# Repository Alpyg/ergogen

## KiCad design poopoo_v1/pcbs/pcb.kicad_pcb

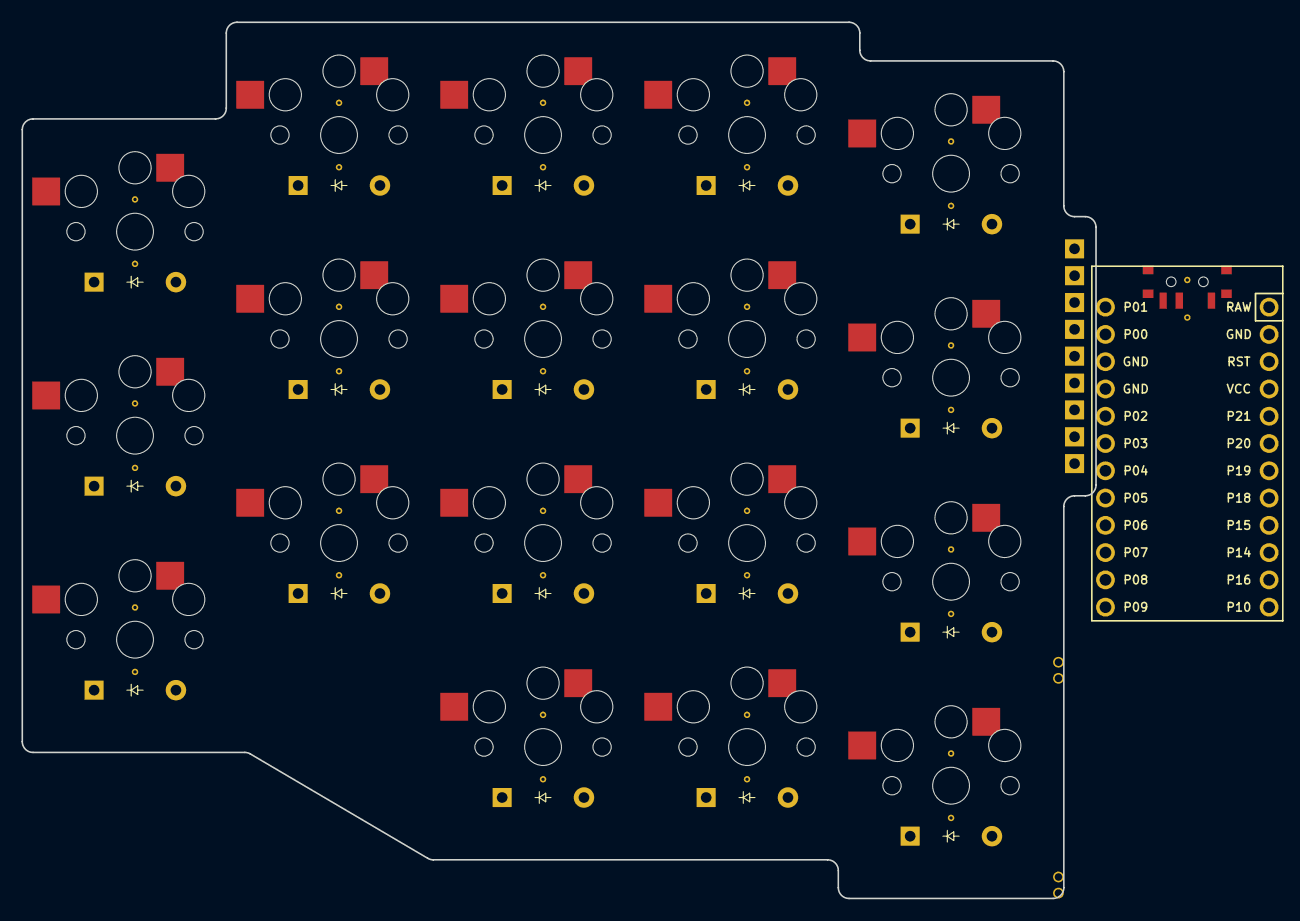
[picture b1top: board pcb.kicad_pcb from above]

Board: 2 copper layers, 100.0 x 81.6 mm, 37 parts (0 on the bottom side), 28 nets, no tracks yet.

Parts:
D1, D2, D3, D4, D5, D6, D7, D8, D9, D10, D11, D12, D13, D14, D15, D16, D17, D18: ComboDiode
MCU1: ProMicro
S1, S2, S3, S4, S5, S6, S7, S8, S9, S10, S11, S12, S13, S14, S15, S16, S17, S18: PG1350

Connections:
GND: MCU1.2, MCU1.15, MCU1.16
col_far: S15.2, S16.2, S17.2, S18.2
col_index: S11.2, S12.2, S13.2, S14.2
col_middle: S7.2, S8.2, S9.2, S10.2
col_pinky: S1.2, S2.2, S3.2
col_ring: S4.2, S5.2, S6.2
home_col_far: D17.2, S17.1
home_col_index: D13.2, S13.1
home_col_middle: D9.2, S9.1
home_col_pinky: D2.2, S2.1
home_col_ring: D5.2, S5.1
inner_col_far: D16.2, S16.1
inner_col_index: D12.2, S12.1
inner_col_middle: D8.2, S8.1
inner_col_pinky: D1.2, S1.1
inner_col_ring: D4.2, S4.1
outer_col_far: D18.2, S18.1
outer_col_index: D14.2, S14.1
outer_col_middle: D10.2, S10.1
outer_col_pinky: D3.2, S3.1
outer_col_ring: D6.2, S6.1
row_home: D2.1, D5.1, D9.1, D13.1, D17.1
row_inner: D1.1, D4.1, D8.1, D12.1, D16.1
row_outer: D3.1, D6.1, D10.1, D14.1, D18.1
row_thumb: D7.1, D11.1, D15.1
thumb_col_far: D15.2, S15.1
thumb_col_index: D11.2, S11.1
thumb_col_middle: D7.2, S7.1

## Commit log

2023-01-16 Added Ben Vallack's footprints
2023-01-28 Revert "Added Ben Vallack's footprints"
    This reverts commit 423b156d2d0c8febfb8dc57614209ea511b82ca3.
2023-10-22 poopoo
2024-06-14 PooVoyager v1
2024-07-09 PooVoyager v2 started
